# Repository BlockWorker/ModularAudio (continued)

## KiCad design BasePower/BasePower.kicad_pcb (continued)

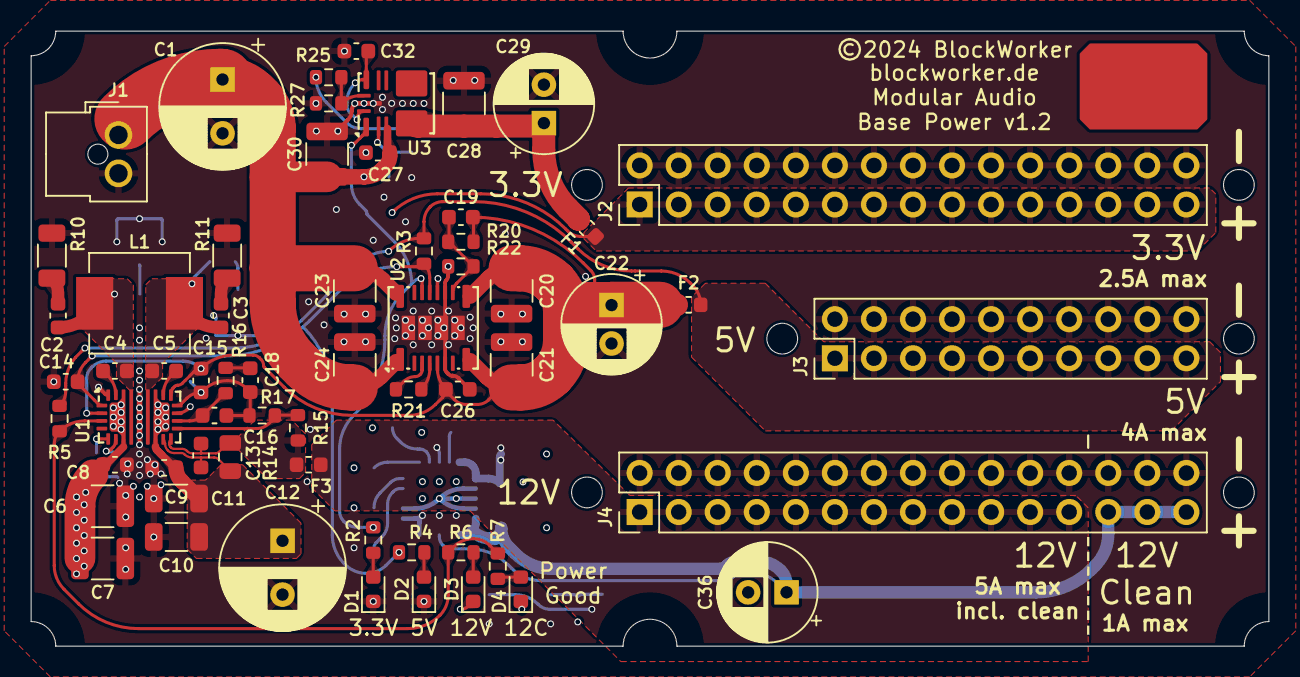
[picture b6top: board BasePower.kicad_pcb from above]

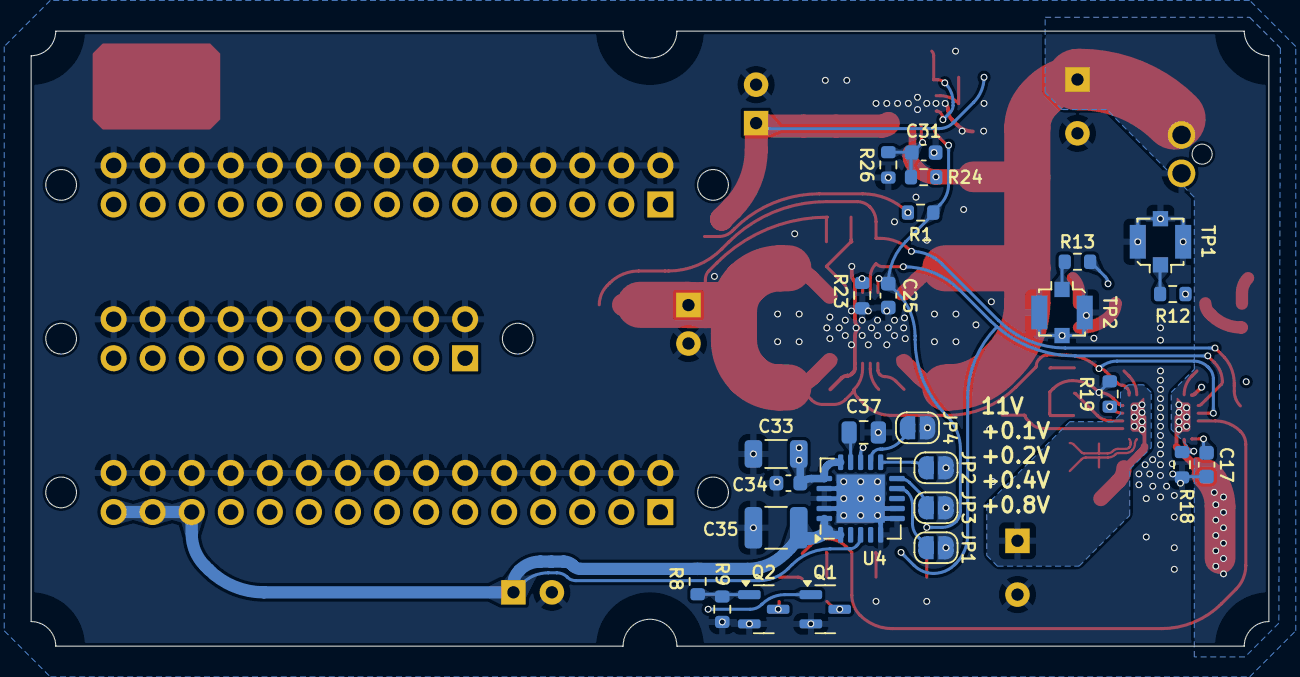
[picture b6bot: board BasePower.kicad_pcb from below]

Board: 4 copper layers, 80.5 x 40.0 mm, 94 parts (26 on the bottom side), 46 nets.

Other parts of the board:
Hole1, Hole2, Hole3, Hole4, Hole5, Hole6: Hole_2mm

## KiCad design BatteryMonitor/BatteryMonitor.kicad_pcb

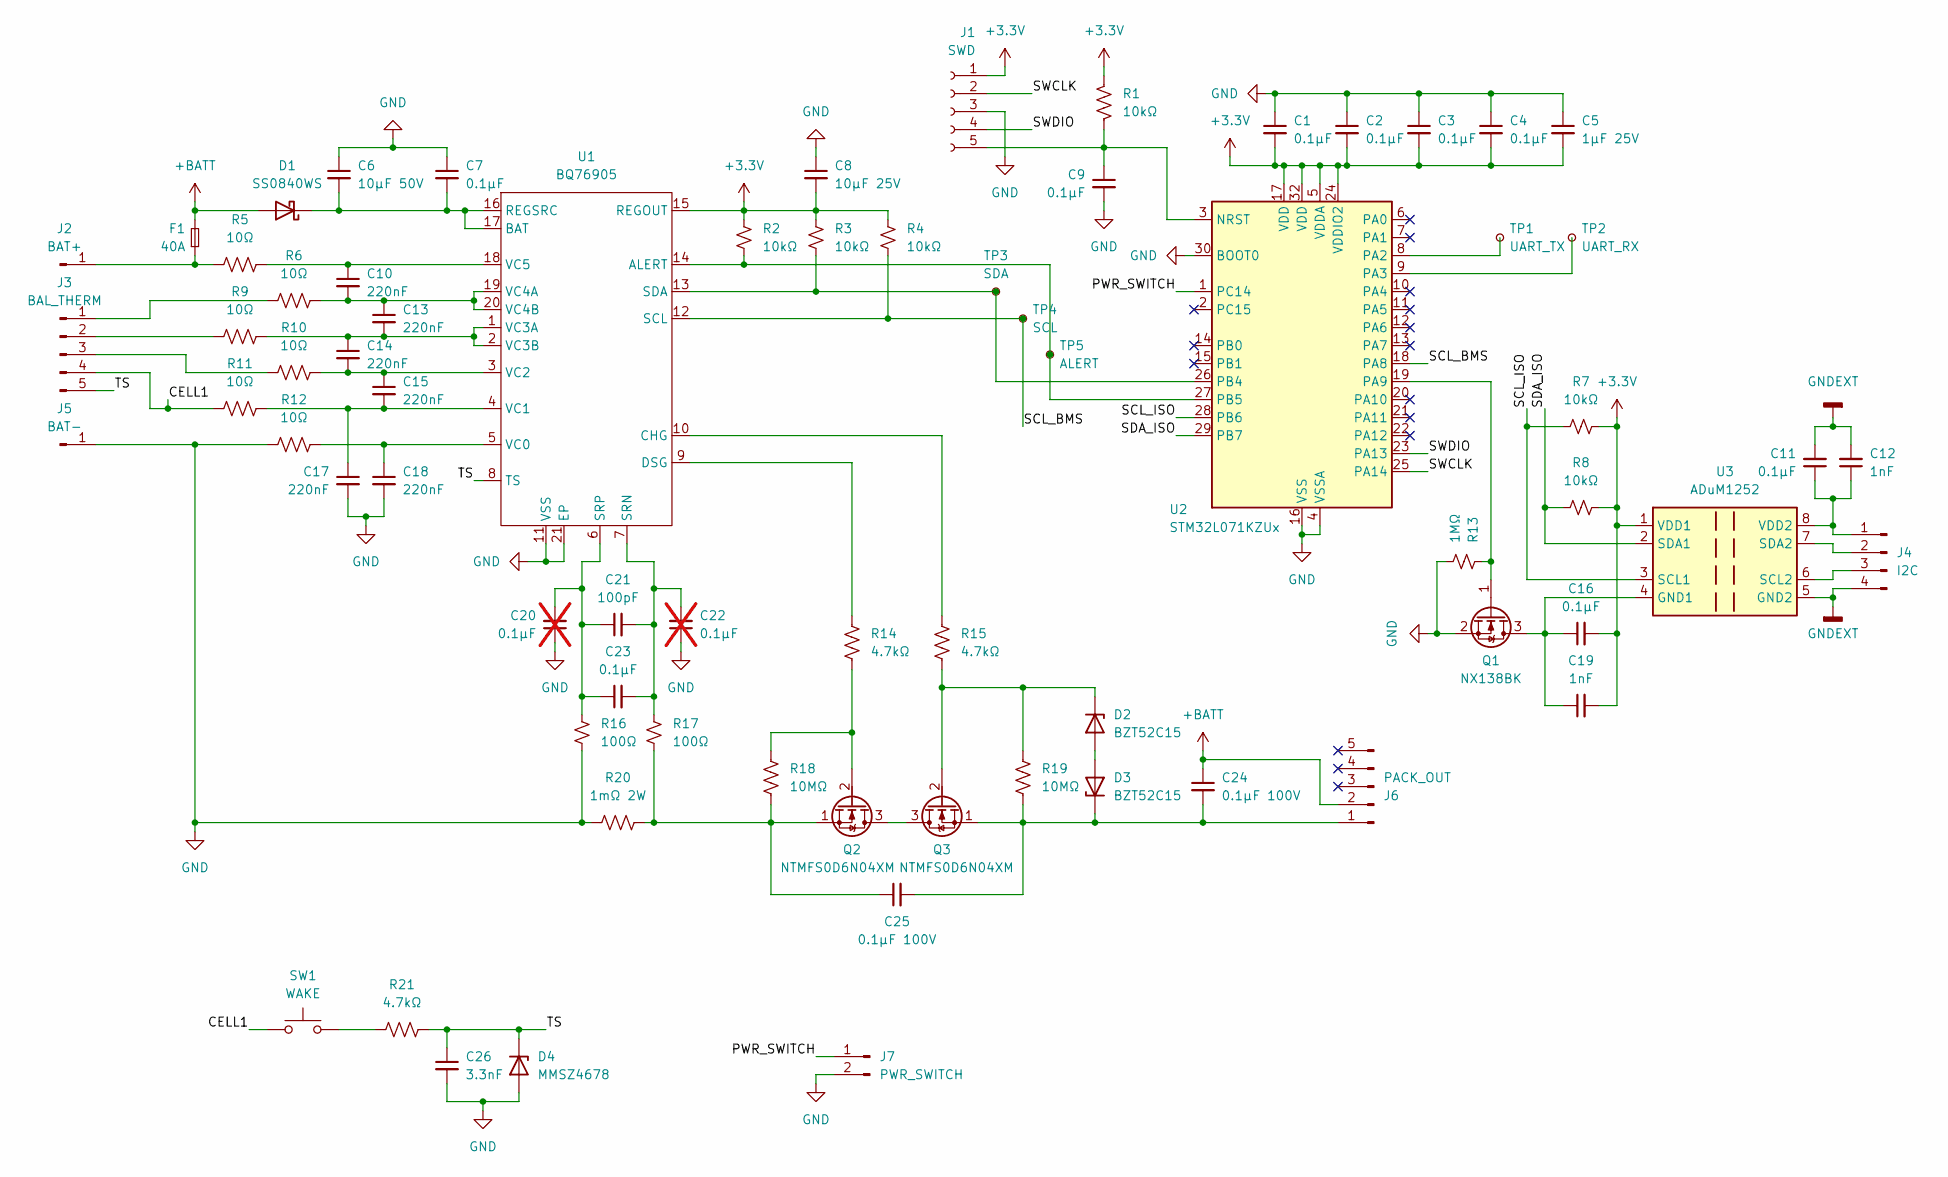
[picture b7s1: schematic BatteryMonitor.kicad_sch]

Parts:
C1, C2, C3, C4, C7, C9, C11, C16, C23: 0.1µF; C_0603_1608Metric
C5: 1µF 25V; C_0603_1608Metric
C6: 10µF 50V; C_1206_3216Metric
C8: 10µF 25V; C_0805_2012Metric
C10, C13, C14, C15, C17, C18: 220nF; C_0603_1608Metric
C12, C19: 1nF; C_0603_1608Metric
C20, C22: 0.1µF; C_0603_1608Metric; not fitted
C21: 100pF; C_0603_1608Metric
C24, C25: 0.1µF 100V; C_0603_1608Metric
C26: 3.3nF; C_0603_1608Metric
D1: SS0840WS; D_SOD-323_HandSoldering
D2, D3: BZT52C15; D_SOD-123
D4: MMSZ4678; D_SOD-123
F1: 40A; Fuse_2410_6125Metric
J1: SWD; PinSocket_1x05_P1.27mm_Vertical_SMD_Pin1Right
J2: BAT+; Wuerth_REDCUBE-THR_WP-BUTR_7461057_NonPress
J3: BAL_THERM; Amphenol_MINITEK_WTB_1.25_5P
J4: I2C; Amphenol_MINITEK_WTB_1.25_4P
J5: BAT-; Wuerth_REDCUBE-THR_WP-BUTR_7461057_NonPress
J6: PACK_OUT; TE_2042274_Solder
J7: PWR_SWITCH; Amphenol_MINITEK_WTB_1.25_2P
Q1: NX138BK; SOT-23-3
Q2, Q3: NTMFS0D6N04XM; ONSemi_SO8-FL_506FA
R1, R2, R3, R4, R7, R8: 10kΩ; R_0603_1608Metric
R5, R6, R9, R10, R11, R12: 10Ω; R_0603_1608Metric
R13: 1MΩ; R_0603_1608Metric
R14, R15, R21: 4.7kΩ; R_0603_1608Metric
R16, R17: 100Ω; R_0603_1608Metric
R18, R19: 10MΩ; R_0603_1608Metric
R20: 1mΩ 2W; R_0612_1632Metric
SW1: WAKE; SW_SPST_TL3305A
TP1: UART_TX; TP_0603_1608Metric_Fused
TP2: UART_RX; TP_0603_1608Metric_Fused
TP3: SDA; TP_0603_1608Metric_Fused
TP4: SCL; TP_0603_1608Metric_Fused
TP5: ALERT; TP_0603_1608Metric_Fused
U1: BQ76905; VQFN-20-1EP_3.5x3.5mm_P0.5mm_EP2.05x2.05mm
U2: STM32L071KZUx; QFN-32-1EP_5x5mm_P0.5mm_EP3.45x3.45mm
U3: ADuM1252; MSOP-8_3x3mm_P0.65mm

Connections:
+3.3V: C1.2, C2.2, C3.2, C4.2, C5.2, C8.2, C16.2, C19.2, J1.1, R1.1, R2.1, R3.1, R4.1, R7.1, R8.1, U1.15 (REGOUT), U2.5 (VDDA), U2.17 (VDD), U2.24 (VDDIO2), U2.32 (VDD), U3.1 (VDD1)
+BATT: C24.1, D1.2 (A), F1.2, J6.2
/CELL1: J3.4, R11.1, SW1.1
/PWR_SWITCH: J7.1, U2.1 (PC14)
/SCL_BMS: R4.2, TP4.1, U1.12 (SCL), U2.18 (PA8)
/SCL_ISO: R7.2, U2.28 (PB6), U3.3 (SCL1)
/SDA_ISO: R8.2, U2.29 (PB7), U3.2 (SDA1)
/SWCLK: J1.2, U2.25 (PA14)
/SWDIO: J1.4, U2.23 (PA13)
/TS: C26.1, D4.1 (K), J3.5, R21.2, U1.8 (TS)
GND: C1.1, C2.1, C3.1, C4.1, C5.1, C6.1, C7.1, C8.1, C9.2, C17.2, C18.2, C20.1, C22.1, C26.2, D4.2 (A), J1.3, J5.1, J7.2, Q1.2 (S), R12.1, R13.2, R16.2, R20.1, U1.11 (VSS), U1.21 (EP), U2.4 (VSSA), U2.16 (VSS), U2.30 (BOOT0), U2.31 (VSS), U2.33 (VSS)
GNDEXT: C11.2, C12.2, J4.4, U3.5 (GND2)
unnamed: C6.2, C7.2, D1.1 (K), U1.16 (REGSRC), U1.17 (BAT)
unnamed: D2.2 (A), D3.2 (A)
unnamed: D2.1 (K), Q3.2 (G), R15.2, R19.1
unnamed: C24.2, C25.2, D3.1 (K), J6.1, Q3.1 (S), R19.2
unnamed: C9.1, J1.5, R1.2, U2.3 (NRST)
unnamed: F1.1, J2.1, R5.1
unnamed: J3.1, R6.1
unnamed: J3.2, R9.1
unnamed: J3.3, R10.1
unnamed: C11.1, C12.1, J4.1, U3.8 (VDD2)
unnamed: J4.2, U3.7 (SDA2)
unnamed: J4.3, U3.6 (SCL2)
unnamed: C16.1, C19.1, Q1.3 (D), U3.4 (GND1)
unnamed: Q1.1 (G), R13.1, U2.19 (PA9)
unnamed: Q2.3 (D), Q3.3 (D)
unnamed: Q2.2 (G), R14.2, R18.1
unnamed: C25.1, Q2.1 (S), R17.2, R18.2, R20.2
unnamed: R21.1, SW1.2
unnamed: R2.2, TP5.1, U1.14 (ALERT), U2.27 (PB5)
unnamed: R15.1, U1.10 (CHG)
unnamed: R14.1, U1.9 (DSG)
unnamed: R3.2, TP3.1, U1.13 (SDA), U2.26 (PB4)
unnamed: C21.2, C22.2, C23.2, R17.1, U1.7 (SRN)
unnamed: C20.2, C21.1, C23.1, R16.1, U1.6 (SRP)
unnamed: C18.1, R12.2, U1.5 (VC0)
unnamed: C15.2, C17.1, R11.2, U1.4 (VC1)
unnamed: C14.2, C15.1, R10.2, U1.3 (VC2)
unnamed: C13.2, C14.1, R9.2, U1.1 (VC3A), U1.2 (VC3B)
unnamed: C10.2, C13.1, R6.2, U1.19 (VC4A), U1.20 (VC4B)
unnamed: C10.1, R5.2, U1.18 (VC5)
unnamed: TP1.1, U2.8 (PA2)
unnamed: TP2.1, U2.9 (PA3)

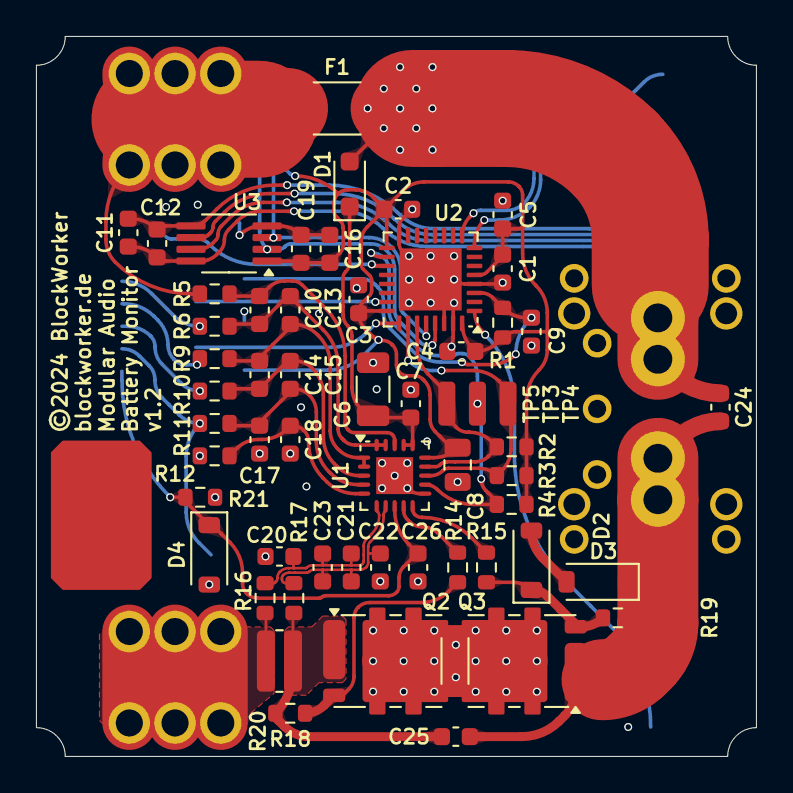
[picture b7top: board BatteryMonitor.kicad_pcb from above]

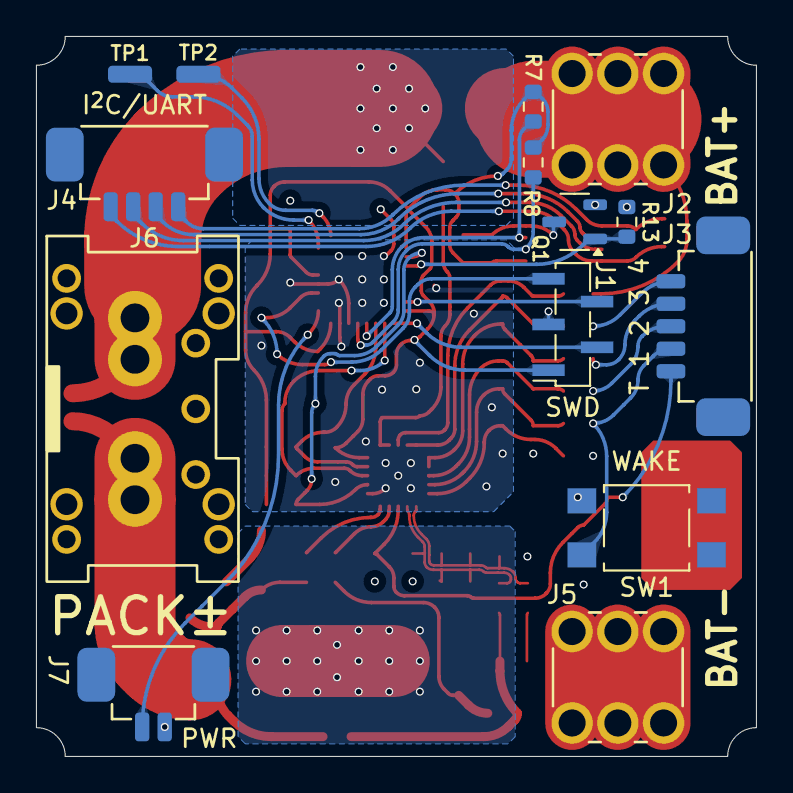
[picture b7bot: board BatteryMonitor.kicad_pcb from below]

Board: 4 copper layers, 40.0 x 40.0 mm, 71 parts (14 on the bottom side), 44 nets.

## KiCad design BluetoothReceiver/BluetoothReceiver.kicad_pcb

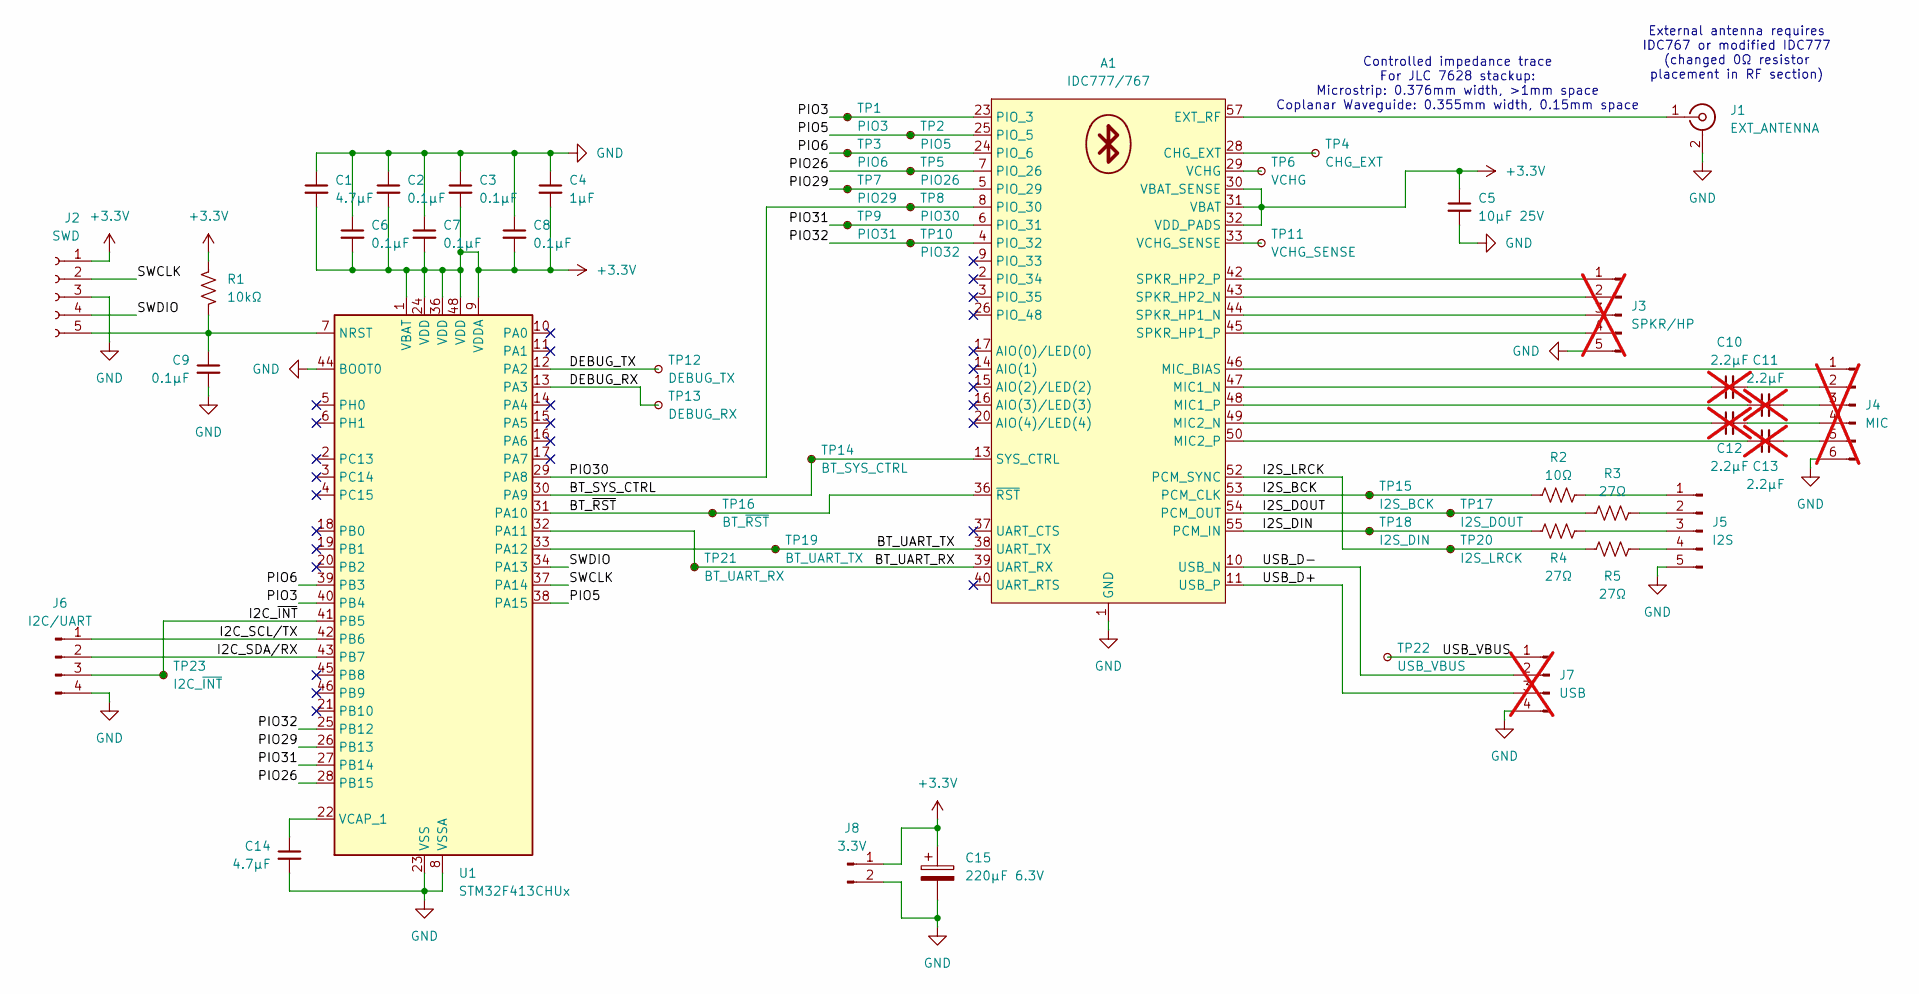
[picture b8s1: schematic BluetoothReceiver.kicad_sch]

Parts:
A1: IDC777/767; IDC777_767
C1, C14: 4.7µF; C_0603_1608Metric
C2, C3, C6, C7, C8, C9: 0.1µF; C_0603_1608Metric
C4: 1µF; C_0603_1608Metric
C5: 10µF 25V; C_0805_2012Metric
C10, C11, C12, C13: 2.2µF; C_0603_1608Metric; not fitted
C15: 220µF 6.3V; CP_Elec_5x5.8
J1: EXT_ANTENNA; U.FL_Molex_MCRF_73412-0110_Vertical
J2: SWD; PinSocket_1x05_P1.27mm_Vertical_SMD_Pin1Right
J3: SPKR/HP; Amphenol_MINITEK_WTB_1.25_5P; not fitted
J4: MIC; Amphenol_MINITEK_WTB_1.25_6P; not fitted
J5: I2S; Amphenol_MINITEK_WTB_1.25_5P
J6: I2C/UART; Amphenol_MINITEK_WTB_1.25_4P
J7: USB; Amphenol_MINITEK_0.8_4P_V; not fitted
J8: 3.3V; Amphenol_MINITEK_WTB_1.25_2P
R1: 10kΩ; R_0603_1608Metric
R2: 10Ω; R_0603_1608Metric
R3, R4, R5: 27Ω; R_0603_1608Metric
TP1: PIO3; TestPoint_Pad_D1.0mm
TP2: PIO5; TestPoint_Pad_D1.0mm
TP3: PIO6; TestPoint_Pad_D1.0mm
TP4: CHG_EXT; TestPoint_Pad_D1.0mm
TP5: PIO26; TestPoint_Pad_D1.0mm
TP6: VCHG; TestPoint_Pad_D1.0mm
TP7: PIO29; TestPoint_Pad_D1.0mm
TP8: PIO30; TestPoint_Pad_D1.0mm
TP9: PIO31; TestPoint_Pad_D1.0mm
TP10: PIO32; TestPoint_Pad_D1.0mm
TP11: VCHG_SENSE; TestPoint_Pad_D1.0mm
TP12: DEBUG_TX; TP_0603_1608Metric_Fused
TP13: DEBUG_RX; TP_0603_1608Metric_Fused
TP14: BT_SYS_CTRL; TP_0603_1608Metric_Fused
TP15: I2S_BCK; TP_0603_1608Metric_Fused
TP16: BT_~{RST}; TP_0603_1608Metric_Fused
TP17: I2S_DOUT; TP_0603_1608Metric_Fused
TP18: I2S_DIN; TP_0603_1608Metric_Fused
TP19: BT_UART_TX; TP_0603_1608Metric_Fused
TP20: I2S_LRCK; TP_0603_1608Metric_Fused
TP21: BT_UART_RX; TP_0603_1608Metric_Fused
TP22: USB_VBUS; TestPoint_Pad_D1.0mm
TP23: I2C_~{INT}; TP_0603_1608Metric_Fused
U1: STM32F413CHUx; QFN-48-1EP_7x7mm_P0.5mm_EP5.6x5.6mm

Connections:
+3.3V: A1.30 (VBAT_SENSE), A1.31 (VBAT), A1.32 (VDD_PADS), C1.2, C2.2, C3.2, C4.2, C5.1, C6.2, C7.2, C8.2, C15.1, J2.1, J8.1, R1.1, U1.1 (VBAT), U1.9 (VDDA), U1.24 (VDD), U1.36 (VDD), U1.48 (VDD)
/BT_SYS_CTRL: A1.13 (SYS_CTRL), TP14.1, U1.30 (PA9)
/BT_UART_RX: A1.39 (UART_RX), TP21.1, U1.32 (PA11)
/BT_UART_TX: A1.38 (UART_TX), TP19.1, U1.33 (PA12)
/BT_~RST: A1.36 (~RST), TP16.1, U1.31 (PA10)
/DEBUG_RX: TP13.1, U1.13 (PA3)
/DEBUG_TX: TP12.1, U1.12 (PA2)
/I2C_SCL/TX: J6.1, U1.42 (PB6)
/I2C_SDA/RX: J6.2, U1.43 (PB7)
/I2C_~INT: J6.3, TP23.1, U1.41 (PB5)
/I2S_BCK: A1.53 (PCM_CLK), R2.1, TP15.1
/I2S_DIN: A1.55 (PCM_IN), R4.1, TP18.1
/I2S_DOUT: A1.54 (PCM_OUT), R3.1, TP17.1
/I2S_LRCK: A1.52 (PCM_SYNC), R5.1, TP20.1
/PIO3: A1.23 (PIO_3), TP1.1, U1.40 (PB4)
/PIO5: A1.25 (PIO_5), TP2.1, U1.38 (PA15)
/PIO6: A1.24 (PIO_6), TP3.1, U1.39 (PB3)
/PIO26: A1.7 (PIO_26), TP5.1, U1.28 (PB15)
/PIO29: A1.5 (PIO_29), TP7.1, U1.26 (PB13)
/PIO30: A1.8 (PIO_30), TP8.1, U1.29 (PA8)
/PIO31: A1.6 (PIO_31), TP9.1, U1.27 (PB14)
/PIO32: A1.4 (PIO_32), TP10.1, U1.25 (PB12)
/SWCLK: J2.2, U1.37 (PA14)
/SWDIO: J2.4, U1.34 (PA13)
/USB_D+: A1.11 (USB_P), J7.3
/USB_D-: A1.10 (USB_N), J7.2
/USB_VBUS: J7.1, TP22.1
GND: A1.1 (GND), A1.12 (GND), A1.18 (GND), A1.19 (GND), A1.21 (GND), A1.22 (GND), A1.27 (GND), A1.34 (GND), A1.35 (GND), A1.41 (GND), A1.51 (GND), A1.56 (GND), A1.58 (GND), A1.59 (GND), A1.60 (GND), C1.1, C2.1, C3.1, C4.1, C5.2, C6.1, C7.1, C8.1, C9.2, C14.2, C15.2, J1.2 (Ext), J2.3, J3.5, J4.6, J5.5, J6.4, J7.4, J8.2, U1.8 (VSSA), U1.23 (VSS), U1.35 (VSS), U1.44 (BOOT0), U1.47 (VSS), U1.49 (VSS)
unnamed: A1.28 (CHG_EXT), TP4.1
unnamed: A1.57 (EXT_RF), J1.1 (In)
unnamed: A1.47 (MIC1_N), C10.1
unnamed: A1.48 (MIC1_P), C11.1
unnamed: A1.49 (MIC2_N), C12.1
unnamed: A1.50 (MIC2_P), C13.1
unnamed: A1.46 (MIC_BIAS), J4.1
unnamed: A1.44 (SPKR_HP1_N), J3.3
unnamed: A1.45 (SPKR_HP1_P), J3.4
unnamed: A1.43 (SPKR_HP2_N), J3.2
unnamed: A1.42 (SPKR_HP2_P), J3.1
unnamed: A1.29 (VCHG), TP6.1
unnamed: A1.33 (VCHG_SENSE), TP11.1
unnamed: C9.1, J2.5, R1.2, U1.7 (NRST)
unnamed: C10.2, J4.2
unnamed: C11.2, J4.3
unnamed: C12.2, J4.4
unnamed: C13.2, J4.5
unnamed: J5.1, R2.2
unnamed: J5.2, R3.2
unnamed: J5.3, R4.2
unnamed: J5.4, R5.2
unnamed: C14.1, U1.22 (VCAP_1)

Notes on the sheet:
Controlled impedance trace For JLC 7628 stackup: Microstrip: 0.376mm width, >1mm space Coplanar Waveguide: 0.355mm width, 0.15mm space
External antenna requires IDC767 or modified IDC777 (changed 0Ω resistor placement in RF section)

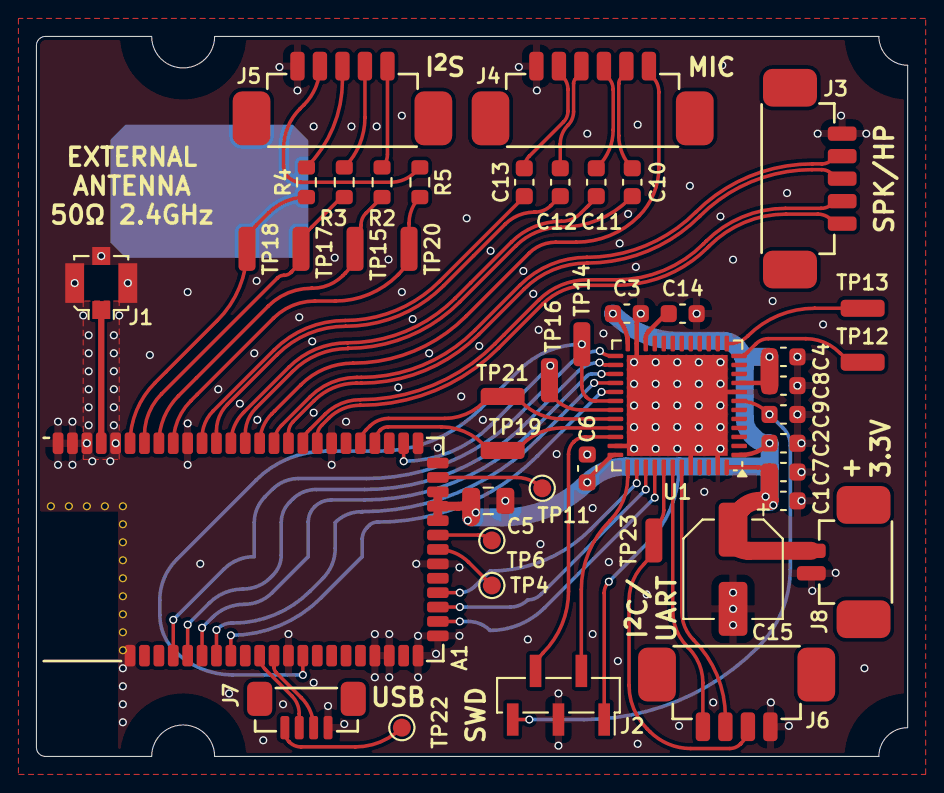
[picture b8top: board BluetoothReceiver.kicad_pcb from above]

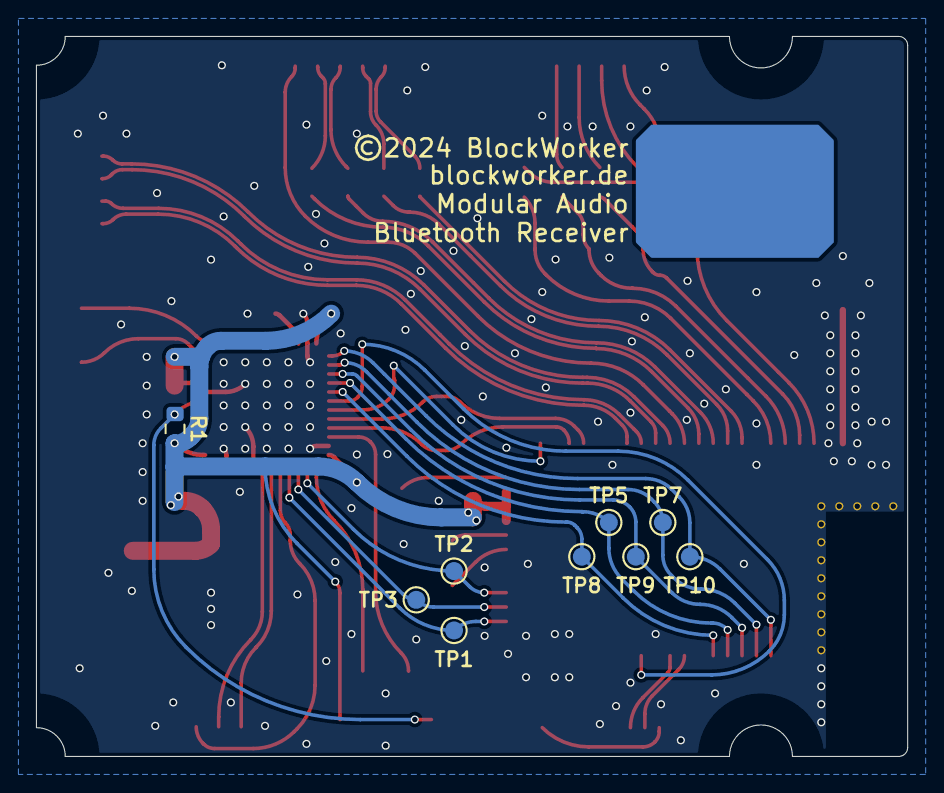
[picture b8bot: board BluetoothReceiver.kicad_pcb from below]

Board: 4 copper layers, 48.4 x 40.0 mm, 53 parts (9 on the bottom side), 51 nets.

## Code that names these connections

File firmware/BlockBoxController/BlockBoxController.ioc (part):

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Mcu.Name=STM32H725VGTx
Mcu.Package=LQFP100
Mcu.UserName=STM32H725VGTx
PA0.GPIOParameters=GPIO_PuPd
PA0.GPIO_PuPd=GPIO_PULLDOWN
PA0.Signal=S_TIM2_CH1_ETR
PA1.GPIOParameters=GPIO_PuPd
PA1.GPIO_PuPd=GPIO_PULLDOWN
PA1.Signal=S_TIM2_CH2
PA10.GPIOParameters=GPIO_PuPd,GPIO_Label
PA10.GPIO_Label=AMP_CLIP_OTW_N
PA10.GPIO_PuPd=GPIO_PULLUP
PA10.Signal=GPIO_Input
PA11.GPIOParameters=GPIO_PuPd,GPIO_Label
PA11.GPIO_Label=AMP_FAULT_N
PA11.GPIO_PuPd=GPIO_PULLUP
PA11.Signal=GPIO_Input
PA12.GPIOParameters=GPIO_PuPd,GPIO_Label
PA12.GPIO_Label=AMP_RESET_N
PA12.GPIO_PuPd=GPIO_PULLUP
PA12.Signal=GPIO_Input
PA13(JTMS/SWDIO).Mode=Serial_Wire
PA13(JTMS/SWDIO).Signal=DEBUG_JTMS-SWDIO
PA14(JTCK/SWCLK).Mode=Serial_Wire
PA14(JTCK/SWCLK).Signal=DEBUG_JTCK-SWCLK
PA15(JTDI).Mode=Half_Duplex_Slave_Rx
PA15(JTDI).Signal=I2S6_WS
PA2.Mode=Asynchronous
PA2.Signal=USART2_TX
PA3.Mode=Asynchronous
PA3.Signal=USART2_RX
PA4.GPIOParameters=GPIO_PuPd,GPIO_Label
PA4.GPIO_Label=LCD_GPIO3
PA4.GPIO_PuPd=GPIO_PULLDOWN
PA4.Signal=GPIO_Input
PA5.GPIOParameters=GPIO_PuPd,GPIO_Label
PA5.GPIO_Label=LCD_GPIO2
PA5.GPIO_PuPd=GPIO_PULLDOWN
PA5.Signal=GPIO_Input
PA6.GPIOParameters=GPIO_PuPd
PA6.GPIO_PuPd=GPIO_PULLUP
PA6.Mode=OCTOSPI1_IOL_Port1L
PA6.Signal=OCTOSPIM_P1_IO3
PA7.GPIOParameters=GPIO_PuPd
PA7.GPIO_PuPd=GPIO_PULLUP
PA7.Mode=OCTOSPI1_IOL_Port1L
PA7.Signal=OCTOSPIM_P1_IO2
PA8.Mode=I2C
PA8.Signal=I2C3_SCL
PB0.GPIOParameters=GPIO_PuPd
PB0.GPIO_PuPd=GPIO_PULLUP
PB0.Mode=OCTOSPI1_IOL_Port1L
PB0.Signal=OCTOSPIM_P1_IO1
PB1.GPIOParameters=GPIO_PuPd
PB1.GPIO_PuPd=GPIO_PULLUP
PB1.Mode=OCTOSPI1_IOL_Port1L
PB1.Signal=OCTOSPIM_P1_IO0
PB10.Mode=OCTOSPI1_Port1_NCS
PB10.Signal=OCTOSPIM_P1_NCS
PB12.GPIOParameters=GPIO_Speed
PB12.GPIO_Speed=GPIO_SPEED_FREQ_HIGH
PB12.Mode=NSS_Signal_Hard_Output
PB12.Signal=SPI2_NSS
PB13.GPIOParameters=GPIO_Speed
PB13.GPIO_Speed=GPIO_SPEED_FREQ_HIGH
PB13.Mode=Full_Duplex_Master
PB13.Signal=SPI2_SCK
PB14.GPIOParameters=GPIO_Speed
PB14.GPIO_Speed=GPIO_SPEED_FREQ_HIGH
PB14.Mode=Full_Duplex_Master
PB14.Signal=SPI2_MISO
PB15.GPIOParameters=GPIO_Speed
PB15.GPIO_Speed=GPIO_SPEED_FREQ_HIGH
PB15.Mode=Full_Duplex_Master
PB15.Signal=SPI2_MOSI
PB2.Mode=O1_P1_CLK
PB2.Signal=OCTOSPIM_P1_CLK
PB3(JTDO/TRACESWO).Mode=Half_Duplex_Slave_Rx
PB3(JTDO/TRACESWO).Signal=I2S6_CK
PB4(NJTRST).Mode=Half_Duplex_Slave_Rx
PB4(NJTRST).Signal=I2S6_SDI
PB5.GPIOParameters=GPIO_PuPd,GPIO_Label,GPIO_ModeDefaultEXTI
PB5.GPIO_Label=I2C1_INT0_N
PB5.GPIO_ModeDefaultEXTI=GPIO_MODE_IT_FALLING
PB5.GPIO_PuPd=GPIO_PULLUP
PB5.Signal=GPXTI5
PB6.Mode=Asynchronous
PB6.Signal=USART1_TX
PB7.Mode=Asynchronous
PB7.Signal=USART1_RX
PB8.Mode=Asynchronous
PB8.Signal=UART4_RX
PB9.Mode=Asynchronous
PB9.Signal=UART4_TX
PC0.Signal=ADCx_INP10
PC1.Signal=ADCx_INP11
PC10.Mode=I2C
PC10.Signal=I2C5_SDA
PC11.Mode=I2C
PC11.Signal=I2C5_SCL
PC12.GPIOParameters=GPIO_PuPd,GPIO_Label,GPIO_ModeDefaultEXTI
PC12.GPIO_Label=I2C5_INT0_N
PC12.GPIO_ModeDefaultEXTI=GPIO_MODE_IT_FALLING
PC12.GPIO_PuPd=GPIO_PULLUP
PC12.Signal=GPXTI12
PC13.GPIOParameters=GPIO_PuPd,GPIO_Label
PC13.GPIO_Label=B1_PLAY
PC13.GPIO_PuPd=GPIO_PULLUP
PC13.Signal=GPIO_Input
PC14-OSC32_IN.GPIOParameters=GPIO_PuPd,GPIO_Label
PC14-OSC32_IN.GPIO_Label=B1_MFB
PC14-OSC32_IN.GPIO_PuPd=GPIO_PULLUP
PC14-OSC32_IN.Signal=GPIO_Input
PC15-OSC32_OUT.GPIOParameters=GPIO_PuPd,GPIO_Label
PC15-OSC32_OUT.GPIO_Label=B1_FWD
PC15-OSC32_OUT.GPIO_PuPd=GPIO_PULLUP
PC15-OSC32_OUT.Signal=GPIO_Input
PC4.GPIOParameters=GPIO_PuPd,GPIO_Label,GPIO_ModeDefaultEXTI
PC4.GPIO_Label=LCD_INT_N
PC4.GPIO_ModeDefaultEXTI=GPIO_MODE_IT_FALLING
PC4.GPIO_PuPd=GPIO_PULLUP
PC4.Signal=GPXTI4
PC5.GPIOParameters=GPIO_Label
PC5.GPIO_Label=LCD_PD_N
PC5.Signal=GPIO_Output
PC8.GPIOParameters=GPIO_PuPd,GPIO_Label,GPIO_ModeDefaultEXTI
PC8.GPIO_Label=CHG_ACOK
PC8.GPIO_ModeDefaultEXTI=GPIO_MODE_IT_RISING_FALLING
PC8.GPIO_PuPd=GPIO_PULLDOWN
PC8.Signal=GPXTI8
PC9.Mode=I2C
PC9.Signal=I2C3_SDA
PD0.GPIOParameters=GPIO_PuPd,GPIO_Label,GPIO_ModeDefaultEXTI
PD0.GPIO_Label=I2C5_INT1_N
PD0.GPIO_ModeDefaultEXTI=GPIO_MODE_IT_FALLING
PD0.GPIO_PuPd=GPIO_PULLUP
PD0.Signal=GPXTI0
PD1.GPIOParameters=GPIO_PuPd,GPIO_Label,GPIO_ModeDefaultEXTI
PD1.GPIO_Label=I2C5_INT2_N
PD1.GPIO_ModeDefaultEXTI=GPIO_MODE_IT_FALLING
PD1.GPIO_PuPd=GPIO_PULLUP
PD1.Signal=GPXTI1
PD10.GPIOParameters=GPIO_PuPd,GPIO_Label
PD10.GPIO_Label=B1_LEDMODE_1
PD10.GPIO_PuPd=GPIO_PULLUP
PD10.Signal=GPIO_Input
PD11.GPIOParameters=GPIO_PuPd,GPIO_Label
PD11.GPIO_Label=B1_LEDMODE_2
PD11.GPIO_PuPd=GPIO_PULLUP
PD11.Signal=GPIO_Input
PD12.GPIOParameters=GPIO_PuPd
PD12.GPIO_PuPd=GPIO_PULLDOWN
PD12.Signal=S_TIM4_CH1
PD13.GPIOParameters=GPIO_PuPd
PD13.GPIO_PuPd=GPIO_PULLDOWN
PD13.Signal=S_TIM4_CH2
PD14.GPIOParameters=GPIO_PuPd
PD14.GPIO_PuPd=GPIO_PULLDOWN
PD14.Signal=S_TIM4_CH3
PD2.GPIOParameters=GPIO_PuPd,GPIO_Label,GPIO_ModeDefaultEXTI
PD2.GPIO_Label=I2C5_INT3_N
PD2.GPIO_ModeDefaultEXTI=GPIO_MODE_IT_FALLING
PD2.GPIO_PuPd=GPIO_PULLUP
PD2.Signal=GPXTI2
PD3.GPIOParameters=GPIO_PuPd,GPIO_Label,GPIO_ModeDefaultEXTI
PD3.GPIO_Label=I2C5_INT4_N
PD3.GPIO_ModeDefaultEXTI=GPIO_MODE_IT_FALLING
PD3.GPIO_PuPd=GPIO_PULLUP
PD3.Signal=GPXTI3
PD9.GPIOParameters=GPIO_PuPd,GPIO_Label
PD9.GPIO_Label=B1_LCD_SWITCH
PD9.GPIO_PuPd=GPIO_PULLUP
PD9.Signal=GPIO_Input
PE2.GPIOParameters=GPIO_PuPd,GPIO_Label
PE2.GPIO_Label=B1_VOL_UP
PE2.GPIO_PuPd=GPIO_PULLUP
PE2.Signal=GPIO_Input
PE4.GPIOParameters=GPIO_PuPd,GPIO_Label
PE4.GPIO_Label=B1_VOL_DOWN
PE4.GPIO_PuPd=GPIO_PULLUP
PE4.Signal=GPIO_Input
PE5.GPIOParameters=GPIO_PuPd,GPIO_Label
PE5.GPIO_Label=B1_BACK
PE5.GPIO_PuPd=GPIO_PULLUP
PE5.Signal=GPIO_Input
PE7.GPIOParameters=GPIO_PuPd,GPIO_Label
PE7.GPIO_Label=LCD_B1_D3
PE7.GPIO_PuPd=GPIO_PULLDOWN
PE7.Signal=GPIO_Input
PE8.GPIOParameters=PinState,GPIO_Label
PE8.GPIO_Label=LCD_BL_DRIVE
PE8.PinState=GPIO_PIN_SET
PE8.Signal=GPIO_Output
RCC.SYSCLKFreq_VALUE=520000000
RCC.SYSCLKSource=RCC_SYSCLKSOURCE_PLLCLK
board=custom

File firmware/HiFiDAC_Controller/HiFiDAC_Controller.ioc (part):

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Mcu.Name=STM32C031K(4-6)Ux
Mcu.Package=UFQFPN32
Mcu.UserName=STM32C031K6Ux
PA1.Mode=Full_Duplex_Master
PA1.Signal=SPI1_SCK
PA10.Mode=Asynchronous
PA10.Signal=USART1_RX
PA13.Mode=Serial_Wire
PA13.Signal=DEBUG_SWDIO
PA14-BOOT0.Mode=Serial_Wire
PA14-BOOT0.Signal=DEBUG_SWCLK
PA2.Mode=Full_Duplex_Master
PA2.Signal=SPI1_MOSI
PA3.GPIOParameters=GPIO_Label
PA3.GPIO_Label=DAC_EN
PA3.Signal=GPIO_Output
PA4.GPIOParameters=PinState,GPIO_Label
PA4.GPIO_Label=SPI1_NSS
PA4.PinState=GPIO_PIN_SET
PA4.Signal=GPIO_Output
PA6.Mode=Full_Duplex_Master
PA6.Signal=SPI1_MISO
PA7.GPIOParameters=GPIO_Label
PA7.GPIO_Label=GPIO1
PA7.Signal=GPIO_Input
PB0.GPIOParameters=GPIO_Label
PB0.GPIO_Label=GPIO2
PB0.Signal=GPIO_Input
PB1.GPIOParameters=GPIO_Label
PB1.GPIO_Label=GPIO3
PB1.Signal=GPIO_Input
PB2.GPIOParameters=GPIO_PuPd,GPIO_Label
PB2.GPIO_Label=GPIO4
PB2.GPIO_PuPd=GPIO_PULLDOWN
PB2.Signal=GPIO_Input
PB6.Mode=I2C
PB6.Signal=I2C1_SCL
PB7.Mode=I2C
PB7.Signal=I2C1_SDA
PB8.GPIOParameters=PinState,GPIO_PuPd,GPIO_Label,GPIO_ModeDefaultOutputPP
PB8.GPIO_Label=I2C_INT_N
PB8.GPIO_ModeDefaultOutputPP=GPIO_MODE_OUTPUT_OD
PB8.GPIO_PuPd=GPIO_NOPULL
PB8.PinState=GPIO_PIN_SET
PB8.Signal=GPIO_Output
PC14-OSCX_IN\ (PC14).Mode=Asynchronous
PC14-OSCX_IN\ (PC14).Signal=USART1_TX
RCC.HSE_VALUE=8000000
RCC.SYSCLKFreq_VALUE=12000000
board=custom

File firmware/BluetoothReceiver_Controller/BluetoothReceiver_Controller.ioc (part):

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Mcu.Name=STM32F413C(G-H)Ux
Mcu.Package=UFQFPN48
Mcu.UserName=STM32F413CHUx
PA10.GPIOParameters=PinState,GPIO_PuPd,GPIO_Label,GPIO_ModeDefaultOutputPP
PA10.GPIO_Label=BT_RST_N
PA10.GPIO_ModeDefaultOutputPP=GPIO_MODE_OUTPUT_OD
PA10.GPIO_PuPd=GPIO_NOPULL
PA10.PinState=GPIO_PIN_SET
PA10.Signal=GPIO_Output
PA11.Mode=Asynchronous
PA11.Signal=USART6_TX
PA12.Mode=Asynchronous
PA12.Signal=USART6_RX
PA13.Mode=Serial_Wire
PA13.Signal=SYS_JTMS-SWDIO
PA14.Mode=Serial_Wire
PA14.Signal=SYS_JTCK-SWCLK
PA15.GPIOParameters=GPIO_PuPd,GPIO_Label
PA15.GPIO_Label=BT_PIO5
PA15.GPIO_PuPd=GPIO_PULLDOWN
PA15.Signal=GPIO_Input
PA2.Mode=Asynchronous
PA2.Signal=USART2_TX
PA3.Mode=Asynchronous
PA3.Signal=USART2_RX
PA8.GPIOParameters=GPIO_PuPd,GPIO_Label
PA8.GPIO_Label=BT_PIO30
PA8.GPIO_PuPd=GPIO_PULLDOWN
PA8.Signal=GPIO_Input
PA9.GPIOParameters=GPIO_Label
PA9.GPIO_Label=BT_SYS_CTRL
PA9.Signal=GPIO_Output
PB12.GPIOParameters=GPIO_PuPd,GPIO_Label
PB12.GPIO_Label=BT_PIO32
PB12.GPIO_PuPd=GPIO_PULLDOWN
PB12.Signal=GPIO_Input
PB13.GPIOParameters=GPIO_PuPd,GPIO_Label
PB13.GPIO_Label=BT_PIO29
PB13.GPIO_PuPd=GPIO_PULLDOWN
PB13.Signal=GPIO_Input
PB14.GPIOParameters=GPIO_PuPd,GPIO_Label
PB14.GPIO_Label=BT_PIO31
PB14.GPIO_PuPd=GPIO_PULLDOWN
PB14.Signal=GPIO_Input
PB15.GPIOParameters=GPIO_Label
PB15.GPIO_Label=BT_PIO26
PB15.Signal=GPIO_Output
PB3.GPIOParameters=GPIO_PuPd,GPIO_Label
PB3.GPIO_Label=BT_PIO6
PB3.GPIO_PuPd=GPIO_PULLDOWN
PB3.Signal=GPIO_Input
PB4.GPIOParameters=GPIO_Label
PB4.GPIO_Label=BT_PIO3
PB4.Signal=GPIO_Output
PB5.GPIOParameters=PinState,GPIO_PuPd,GPIO_Label,GPIO_ModeDefaultOutputPP
PB5.GPIO_Label=I2C_INT_N
PB5.GPIO_ModeDefaultOutputPP=GPIO_MODE_OUTPUT_OD
PB5.GPIO_PuPd=GPIO_NOPULL
PB5.PinState=GPIO_PIN_SET
PB5.Signal=GPIO_Output
PB6.Mode=Asynchronous
PB6.Signal=USART1_TX
PB7.Mode=Asynchronous
PB7.Signal=USART1_RX
RCC.SYSCLKFreq_VALUE=100000000
RCC.SYSCLKSource=RCC_SYSCLKSOURCE_PLLCLK
board=custom

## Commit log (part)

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2024-07-11 Initial commit: CleanLVSupply first layout
2024-07-12 CleanLVSupply design done for now
2024-07-13 CleanLVSupply fixes, HiFiDAC skeleton
2024-07-14 HiFiDAC progress
2024-07-14 HiFiDAC renumbered and footprints assigned
2024-07-15 HiFiDAC redesign of clocking, digital IO, ferrite beads
2024-07-16 HiFiDAC PCB reference placement, text, and cleanup
2024-07-17 CleanLVSupply, HiFiDAC adjustments, first order version
2024-07-23 USB Audio credits and license
2024-07-27 CleanLVSupply reduce -17V switch frequency
2024-08-04 PowerAmplifier initial design mostly done
2024-08-07 PowerAmpSupply FET change and layout progress
2024-08-12 PowerAmpSupply final + ICL, PowerAmp final
2024-08-14 HiFiDAC minor fixes (v1.1)
2024-08-27 HiFiDAC testing (v1 failed), PowerAmpSupply order
2024-08-30 HiFiDAC v2 progress
2024-09-13 HiFiDAC v2 ordered version
2024-09-15 PowerAmpSupply coax test connectors
2024-09-16 PowerAmplifier inventory check pre-order
2024-09-21 HiFiDAC firmware progress
2024-09-29 BatteryMonitor initially done, BatteryCharger start
2024-10-03 BatteryCharger pcb progress
2024-10-04 BatteryCharger board initially done
2024-10-09 PowerAmp firmware progress ADC testing
2024-10-13 PowerAmplifier firmware progress
2024-10-18 PowerAmpController I2C initially done
2024-10-20 PowerAmpController enable watchdogs
2024-10-22 PowerAmpController implement init interrupt
2024-10-27 BasePower layout mostly done
2024-10-27 PowerAmpController lower UART IRQ priority
2024-10-29 BatteryMonitor v1.1: I2C swap, isolation
2024-11-01 Remove unnecessarily tracked files
2024-11-03 I2CMonitorApp start
2024-11-05 DigitalAudioProcessor basic planning
2024-11-08 Digital filter testing in Python
2024-12-13 BasePower v1.1: Now with fuses
2024-12-28 BasePower v1.2 + inventory
    Added 12V clean LDO and improved power good display
2024-12-30 DigitalAudioProcessor PCB done
2025-01-01 BluetoothReceiver schematic done
2025-01-02 BluetoothReceiver design done
2025-01-03 BlockBoxController schematic done for now
2025-01-05 Inventory done and ordered
2025-01-07 Corner/side washer design for module mounting
2025-01-09 Backup info sheet
2025-01-15 BatteryMonitor firmware start
2025-01-18 BatteryMonitor controller BMS comms established
    Tested to some extent
2025-01-24 BatteryMonitor current calibration done
2025-01-27 BatteryMonitor controller state-of-charge calculation
    Still needs testing
2025-01-31 BatteryMonitor Controller small features
    Low-voltage powerdown, latching charge faults, fault recovery on powerdown, changed external I2C to UART (needs testing)
2025-02-23 BlockBoxController minimal firmware
2025-02-25 BlockBoxController display firmware driver done
2025-03-01 BlockBoxController GUI basics and testing
2025-03-02 BluetoothReceiver firmware IOT777 defines
2025-03-06 BluetoothReceiver firmware renames
    More sensible prefix for Bluetooth module driver stuff
2025-03-09 BluetoothReceiver firmware done for now
    Added host communication driver and interoperability with BT driver
2025-03-17 BatteryCharger testing + small fix
    U2 voltage source was incorrect
2025-03-22 Minor firmware fixes, preparations for HiFiDAC I2C
2025-03-24 HiFiDAC firmware I2C progress
2025-03-28 DigitalAudioProcessor firmware RAM section definition
    BSS and Data sections with corresponding startup code
    Also set the SAI clock to internal for now, for testing
2025-03-30 DAP firmware more core and memory setup
    Enabled MPU, RAM code moved to ITCMRAM (incl. DSP library), stack moved to DTCMRAM, heap allocation adjusted accordingly
2025-03-31 DAP MATLAB filter design initially done
2025-03-31 DAP firmware fractional FIR implemented
    Reimplemented modified form of CMSIS-DSP FIR processing, optimised for this use case
2025-04-01 DAP firmware SRC progress
    Input sample processing done, barring errors
2025-04-03 DAP firmware SRC testing and debugging
2025-04-04 DAP firmware SRC stabilised
    Now based on mean input rate (direct control) and buffer level (PI control)
2025-04-05 DAP firmware signal processing start
    Also disabled IWDG because it was failing to initialise (???)
2025-04-05 DAP firmware signal processing progress
    Mixer and biquads added
2025-04-07 Updated BMS idle tracking
    Might have used it a bit in between, not very clean... need to get at least one more data point with no usage until then
2025-04-08 DAP firmware input selection logic done for now
2025-04-09 Firmwares updated to new STM32CubeIDE version
2025-04-09 DAP firmware I2C beginnings
2025-04-10 DAP firmware support positive gains; I2C testing
2025-04-18 DAP firmware SPDIF implemented
2025-04-20 I2CMonitorApp RTC and EEPROM windows
    All seems to work fine in testing
    EEPROM write buffer 32B instead of 64B
2025-04-25 I2CMonitorApp added tolerance for some comm errors
    No longer disconnects instantly on the first error
2025-04-26 BatteryCharger v1.2: Increased input voltage range
    Now 17.5V min instead of 19.5V min, to avoid power cycling at startup due to inrush
2025-05-04 DAP firmware MPU: set peripherals as device memory
    Should have really been done all along - surprised it even worked correctly in the previous state
2025-05-07 BlockBoxController move to exception-based model
2025-05-11 BlockBoxController async I2C implemented
    Tested only with CRC so far, also missing interrupt pin handling
2025-05-16 BlockBoxController UART module interface implemented
    Not tested yet
2025-07-06 BlockBoxController register-based UART interface
2025-07-09 BlockBoxController callback refactoring
    Switched to std::function instead of function pointers
2025-07-10 BlockBoxController register-based interface improvements
    Shadowed base transfer functions: new implementations imply/check transfer lengths using register set specification
2025-07-11 BlockBoxController BluetoothReceiver interface basic testing and fixes
2025-07-11 BlockBoxController interrupt-enabled I2C module interface
2025-07-12 BlockBoxController BluetoothReceiver interface improvements
2025-07-13 BlockBoxController BluetoothReceiver+DAP combined testing
2025-07-15 PowerAmpController firmware safety improvement
    Small change to the initialisation code, so that the DAC output is initialised faster, resulting in a shorter dead-time and therefore a shorter/smaller PVDD transient
2025-07-17 UI design started
2025-07-18 UI design progress - input dropdown
2025-07-18 UI design progress - main screen basics
    Missing touch areas
2025-07-19 BlockBoxController refactored events out of ModuleInterface
    This way, other classes (that aren't module interfaces) can become event sources too
2025-07-20 PowerAmpController raised I2C interrupt priority
    Higher priority than ADC interrupts now.
    While this goes against the importance order (ADC is most important for safety), the I2C interrupts are always fast to handle (shouldn't affect safety calculation speed much), and this avoids locking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
2025-07-22 BlockBoxController more move semantics for callbacks
    Not sure if this will actually do anything, but may in theory reduce memory allocations?
2025-07-22 BlockBoxController implemented touch debouncing
    Mostly to ensure the touch is really there/gone before reporting that to the screens; and that EVE has had enough time to update the tag+tracker registers
2025-07-22 BlockBoxController EventSource signature change
    Event callbacks receive a pointer to the source now, instead of a reference, to allow easy pointer comparisons.
2025-07-24 BlockBoxController AudioPathManager progress
    Init, event + power state handling, and Bluetooth updates done. Still untested.
2025-07-26 BlockBoxController AudioPathManager input check improvement
    GetActiveInput should be fast and const - check for input correctness periodically in loop instead
2025-07-26 BlockBoxController HiFiDAC interface fix
    Lesson learned: Unnamed bits in bit fields may have any state - make sure to mask them out when using the value.
2025-07-26 BlockBoxController Bluetooth volume improvements
    AudioPathManager should no longer send unnecessary Bluetooth volume updates to the device
2025-07-27 BlockBoxController AudioPathManager behaviour fixes
    Prevent wrong/unnecessary Bluetooth volume writes on power-off, fix mute synchronisation with Bluetooth device, and make sure Bluetooth volume is read upon a new connection
2025-07-30 USBPanel schematic
    Module/PCB for USB Type-C I/O (charging and data)
2025-08-01 USBPanel PCB complete
2025-08-05 UI design: Settings screens started
2025-08-06 UI design: Settings progress
2025-08-08 PowerAmpController firmware improvements
    - Significantly increased maximum fast and instantaneous safety limits, since we may want those to be higher for powerful drivers
    - Fixed I2C interrupt priorities
    - Implemented clipping and OTW detection to differentiate between event types on the CLIP_OTW pin (based on timing)
2025-08-08 BlockBoxController settings GUI progress
    Audio screen 2/3 pages done
2025-08-09 BlockBoxController implemented display brightness and sleep
    Including NVM storage for those and a few other values.
2025-08-09 BlockBoxController GUI touch tracker smoothing
    Should hopefully prevent most glitches/jumps on sliders
2025-08-10 BlockBoxController implemented RTC interface
2025-08-11 BlockBoxController heap usage monitoring
2025-08-11 BlockBoxController AmpManager implementation started
    Safety limit writing and PVDD tracking with volume done (partially tested).
2025-08-12 BlockBoxController AmpManager status responses added
    Responds to safety warning, clipping, and overtemperature. Also logs faults.
    Implemented limit adjustment in settings GUI - TODO: need to shutdown amp first!
2025-08-12 Changed module reset signalling method over I2C
    Before: interrupt with returned register value 0, now: interrupt with reset-specific flag set; more robust this way.
    Also improved robustness of BlockBoxController I2C interface blocking transfer functions.
2025-08-13 DigitalAudioProcessor increased I2C interrupt priorty
    Reduces communication errors. Doesn't seem to affect DAP operation negatively, but may need to monitor this further.
2025-08-15 PowerAmpSupply EMI measurement
    Attempted some mitigation, with limited success
2025-08-19 PowerAmp instability investigation, controller died
    PowerAmpSupply was likely at fault, removed diode D1, seems to have fixed it.
    PowerAmp controller died, so removed references to it in BlockBoxController for now (until replaced).
2025-08-21 USBPanel small footprint fix
2025-08-22 DAP firmware shortened USB flush/reset timeouts
    Shouldn't cause any issues in normal operation (still quite generous time), but prevents freeze+reset in weird USB disconnect situations
2025-08-25 BlockBoxController implemented battery interface
    Including a few small testing-based changes.
2025-08-27 PowerAmpSupply additional startup simulations
    Trying to see whether soft-start would prevent inrush-limit issues, results inconclusive
2025-08-28 BlockBoxController removed charger current measurement
    Seems like this ADC setup is just too unstable. Not critical anyway.
2025-08-29 BatteryMonitor firmware usability improvements
    Lowered full-charge voltage (matches SoC approximation 100%-level now).
    End-of-discharge shutdown no longer able to trigger while charging (allowing recharge after light-moderate overdischarge).
2025-08-30 BlockBoxController added power settings screen
    Including auto-shutdown and charging behaviour testing, and related bug fixes.
    TODO: battery remaining time estimation
2025-09-01 Amp controller repaired, re-enabled in BlockBoxController
    Basic testing appears to work fine
2025-09-01 BlockBoxController implemented debug menu
    Events page empty for now, need to implement logging.
    Also increased BluetoothReceiver init timeout, to allow for longer init after OTA FW upgrade disable.
2025-09-09 BlockBoxController logging UI implemented
    Scrolling and expand/contract seems to work great
2025-09-11 BlockBoxController debug logging rolled out
    Replaced most messages with log calls.
2025-09-16 BlockBoxController temporarily disabled LEDs
    Recurring LED driver damage, even at low duty cycle, during normal operation - needs more investigation
